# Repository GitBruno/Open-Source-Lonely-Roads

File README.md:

# Open Source Lonely Roads
An active linear power distribution board for Eurorack.

> __WARNING!__ ⚡️ Please be aware of the risks associated with electronics and take relevant precautions.

## Features
- High voltage distribution boards
- Dedicated linear regulators for each header
- Switchable status LEDs
- Star grounding on dedicated layer
- Wide traces
- Reverse voltage protection
- Bypass capacitors
- Ultra low noise
- Ultra low inter-module noise
- Protection + safety features
- 3u boat compatible
- Standard 84hp (19”) and 104hp compatible
- Wide range of voltage input options
- Multiple CV/Gate busses possible. (Have conflicting modules play nice together)
- Optional addons (Voltage converter/startup delay)

Please read the [Wiki](https://github.com/GitBruno/Open-Source-Lonely-Roads/wiki) to find out more about this project.

## Licence
Open Source Lonely Roads by [Robert D Jordan](http://www.catfullofghosts.com/) and [Bruno Herfst](http://brunoherfst.com/) is licensed under a [Creative Commons Attribution 4.0 International License](LICENCE.md).

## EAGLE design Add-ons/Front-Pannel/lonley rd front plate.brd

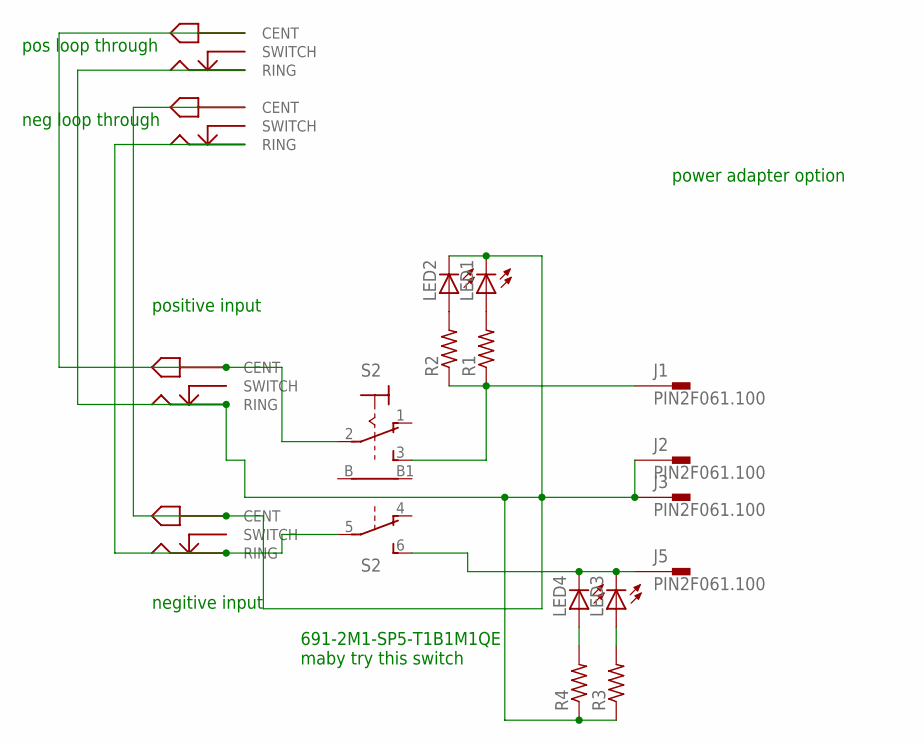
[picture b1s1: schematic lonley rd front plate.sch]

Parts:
J1, J2, J3, J5: PIN2F061.100; F061.100
LED1, LED2, LED3, LED4: LED3MM
R1, R2, R3, R4: R-US_0309/V; 0309V
S2: 9070-2W
U$1, U$2, U$3, U$4: PJ-066A_DC_JACK

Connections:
unnamed: LED2.A, R2.2
unnamed: J2.A1, J2.A2, J3.A1, J3.A2, LED1.K (C), LED2.K (C), R3.1, R4.1, U$1.RING, U$2.CENT, U$3.RING, U$4.CENT
unnamed: J1.A1, J1.A2, R1.1, R2.1, S2.3 (S)
unnamed: J5.A1, J5.A2, LED3.K (C), LED4.K (C)
unnamed: S2.2, U$1.CENT, U$3.CENT
unnamed: U$2.RING, U$4.RING
unnamed: LED1.A, R1.2
unnamed: LED3.A, R3.2
unnamed: LED4.A, R4.2

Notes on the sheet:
positive input
negitive input
pos loop through
neg loop through
691-2M1-SP5-T1B1M1QE maby try this switch
power adapter option

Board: 2 copper layers, 17 parts (0 on the bottom side), 9 nets, no tracks yet.

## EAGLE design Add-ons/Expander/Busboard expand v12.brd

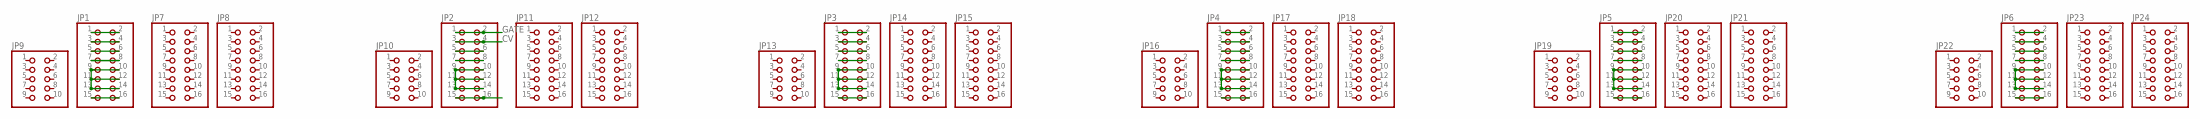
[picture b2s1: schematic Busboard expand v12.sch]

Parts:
JP1, JP2, JP3, JP4, JP5, JP6: PINHD-2X8; 2X08
JP7, JP8, JP11, JP12, JP14, JP15, JP17, JP18, JP20, JP21, JP23, JP24: PINHD-2X8/90; 2X08/90
JP9, JP10, JP13, JP16, JP19, JP22: PINHD-2X5; 2X05

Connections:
CV: JP1.3, JP1.4, JP2.3, JP2.4, JP3.3, JP3.4, JP4.3, JP4.4, JP5.3, JP5.4, JP6.3, JP6.4
GATE: JP1.1, JP1.2, JP2.1, JP2.2, JP3.1, JP3.2, JP4.1, JP4.2, JP5.1, JP5.2, JP6.1, JP6.2
unnamed: JP2.9, JP2.10, JP2.11, JP2.12, JP2.13, JP2.14
unnamed: JP3.9, JP3.10, JP3.11, JP3.12, JP3.13, JP3.14
unnamed: JP1.9, JP1.10, JP1.11, JP1.12, JP1.13, JP1.14
unnamed: JP3.15, JP3.16
unnamed: JP4.9, JP4.10, JP4.11, JP4.12, JP4.13, JP4.14
unnamed: JP1.15, JP1.16
unnamed: JP5.9, JP5.10, JP5.11, JP5.12, JP5.13, JP5.14
unnamed: JP1.7, JP1.8
unnamed: JP4.15, JP4.16
unnamed: JP6.9, JP6.10, JP6.11, JP6.12, JP6.13, JP6.14
unnamed: JP6.15, JP6.16
unnamed: JP6.7, JP6.8
unnamed: JP2.15, JP2.16
unnamed: JP2.5, JP2.6
unnamed: JP1.5, JP1.6
unnamed: JP2.7, JP2.8
unnamed: JP3.5, JP3.6
unnamed: JP5.15, JP5.16
unnamed: JP5.7, JP5.8
unnamed: JP3.7, JP3.8
unnamed: JP4.7, JP4.8
unnamed: JP4.5, JP4.6
unnamed: JP5.5, JP5.6
unnamed: JP6.5, JP6.6

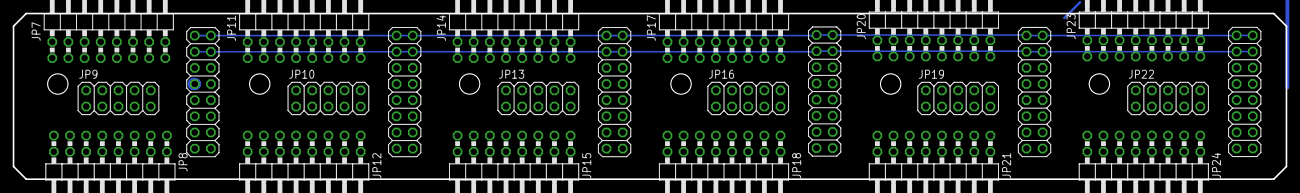
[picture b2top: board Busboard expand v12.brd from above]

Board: 2 copper layers, 200.2 x 26.1 mm, 24 parts (0 on the bottom side), 26 nets.

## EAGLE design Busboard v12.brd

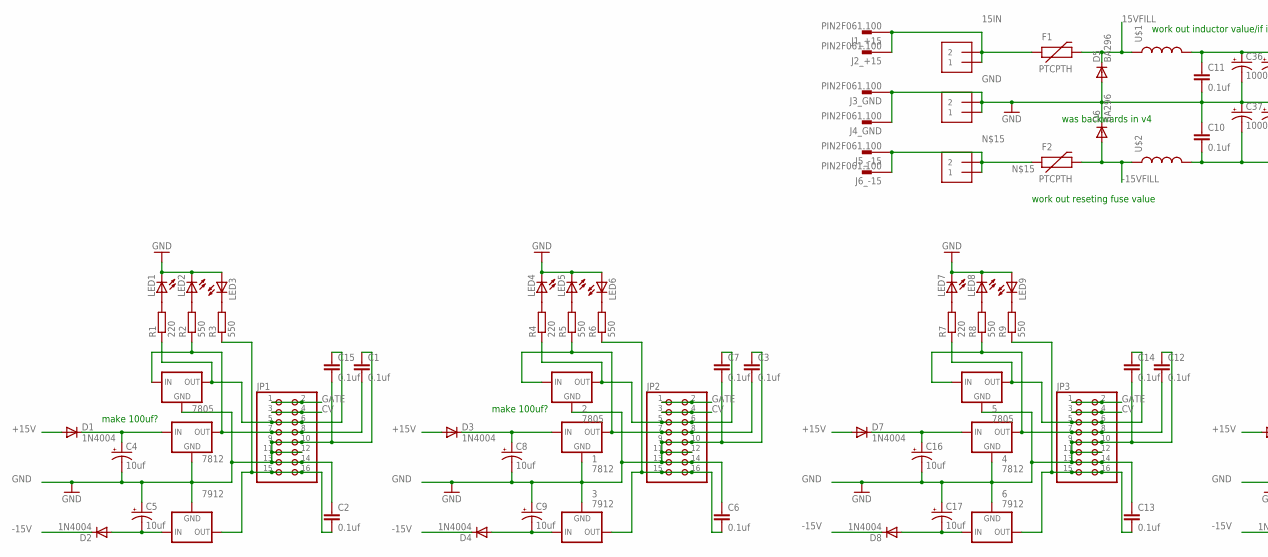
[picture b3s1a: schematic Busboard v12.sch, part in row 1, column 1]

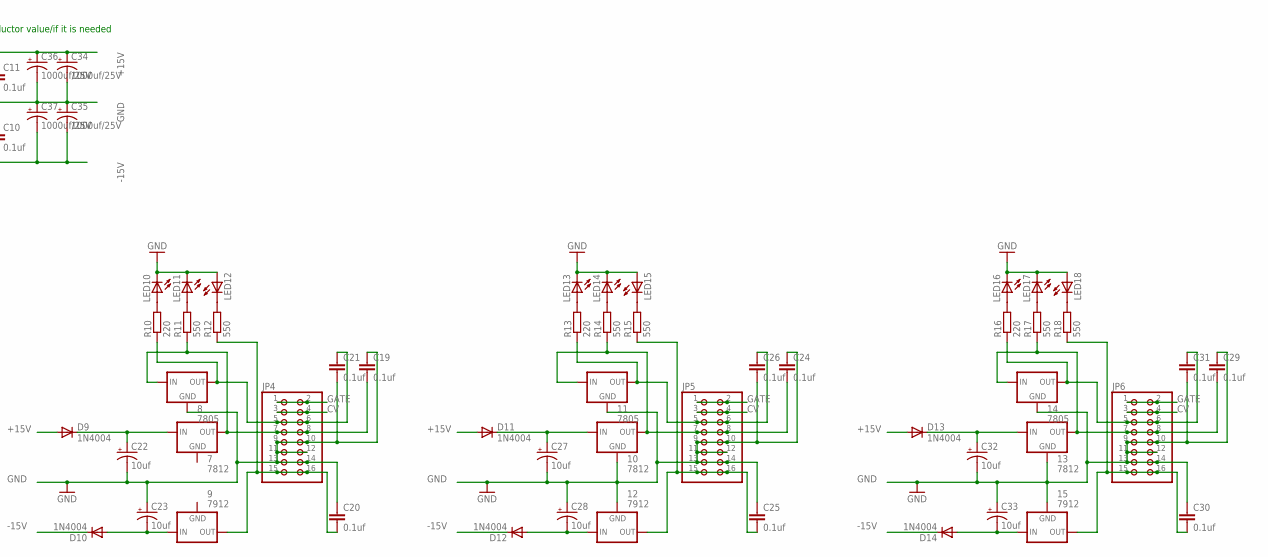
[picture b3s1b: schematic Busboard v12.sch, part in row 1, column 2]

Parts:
1, 4, 7, 10, 13: 7812; 78MXXS
2, 5, 8, 11, 14: 7805; 78MXXS
3, 6, 9, 12, 15: 7912; 79XXS
7805, 7812: 78MXXS
7912: 79XXS
+15V: 1X2-3.5MM
-15V: 1X2-3.5MM
C1, C2, C3, C6, C7, C10, C11, C12, C13, C14, C15, C19, C20, C21, C24, C25, C26, C29, C30, C31: 0.1uf; CAP-PTH-SMALL-KIT
C4, C5, C8, C9, C16, C17, C22, C23, C27, C28, C32, C33: 10uf; CPOL-RADIAL-10UF-25V
C34, C35, C36, C37: 1000uf/25V; CPOL-RADIAL-1000UF-25V-KIT
D1, D2, D3, D4, D7, D8, D9, D10, D11, D12, D13, D14: 1N4004; DO41-10
D5, D6: BA296; P2-15
F1, F2: PTCPTH; PTC
GND: 1X2-3.5MM
J1_+15, J2_+15, J3_GND, J4_GND, J5_-15, J6_-15: PIN2F061.100; F061.100
JP1, JP2, JP3, JP4, JP5, JP6: PINHD-2X8; 2X08
LED1, LED2, LED3, LED4, LED5, LED6, LED7, LED8, LED9, LED10, LED11, LED12, LED13, LED14, LED15, LED16, LED17, LED18: LED3MM
R1, R4, R7, R10, R13, R16: 220; 0207/5V
R2, R3, R5, R6, R8, R9, R11, R12, R14, R15, R17, R18: 550; 0207/5V
U$1, U$2: INDUCTORRLB0912; RLB0912

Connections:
15IN: +15V.1, +15V.2, F1.P$1 (1), J1_+15.A1, J1_+15.A2, J2_+15.A1, J2_+15.A2
15VFILL: D5.C, F1.P$2 (2), U$1.1
+15V: C11.1, C34.+, C36.+, D1.A, D3.A, D7.A, D9.A, D11.A, D13.A, U$1.2
-15V: C10.2, C35.-, C37.-, D2.C, D4.C, D8.C, D10.C, D12.C, D14.C, U$2.2
-15VFILL: D6.A, F2.P$2 (2), U$2.1
CV: JP1.3, JP1.4, JP2.3, JP2.4, JP3.3, JP3.4, JP4.3, JP4.4, JP5.3, JP5.4, JP6.3, JP6.4
GATE: JP1.1, JP1.2, JP2.1, JP2.2, JP3.1, JP3.2, JP4.1, JP4.2, JP5.1, JP5.2, JP6.1, JP6.2
GND: 1.GND, 2.GND, 3.GND, 4.GND, 5.GND, 6.GND, 8.GND, 10.GND, 11.GND, 12.GND, 13.GND, 14.GND, 15.GND, 7805.GND, 7812.GND, 7912.GND, C1.1, C2.1, C3.1, C4.2 (-), C5.1 (+), C6.1, C7.2, C8.2 (-), C9.1 (+), C10.1, C11.2, C12.1, C13.1, C14.2, C15.2, C16.2 (-), C17.1 (+), C19.1, C20.1, C21.2, C22.2 (-), C23.1 (+), C24.1, C25.1, C26.2, C27.2 (-), C28.1 (+), C29.1, C30.1, C31.2, C32.2 (-), C33.1 (+), C34.-, C35.+, C36.-, C37.+, D5.A, D6.C, GND.1, GND.2, J3_GND.A1, J3_GND.A2, J4_GND.A1, J4_GND.A2, JP1.9, JP1.10, JP1.11, JP1.12, JP1.13, JP1.14, JP2.9, JP2.10, JP2.11, JP2.12, JP2.13, JP2.14, JP3.9, JP3.10, JP3.11, JP3.12, JP3.13, JP3.14, JP4.9, JP4.10, JP4.11, JP4.12, JP4.13, JP4.14, JP5.9, JP5.10, JP5.11, JP5.12, JP5.13, JP5.14, JP6.9, JP6.10, JP6.11, JP6.12, JP6.13, JP6.14, LED1.K (C), LED2.K (C), LED3.A, LED4.K (C), LED5.K (C), LED6.A, LED7.K (C), LED8.K (C), LED9.A, LED10.K (C), LED11.K (C), LED12.A, LED13.K (C), LED14.K (C), LED15.A, LED16.K (C), LED17.K (C), LED18.A
unnamed: 7912.IN, C5.2 (-), D2.A
unnamed: 7912.OUT, C2.2, JP1.15, JP1.16, R3.1
unnamed: 6.OUT, C13.2, JP3.15, JP3.16, R9.1
unnamed: 7812.IN, C4.1 (+), D1.C
unnamed: 7805.IN, 7812.OUT, C1.2, JP1.7, JP1.8, R2.1
unnamed: 3.OUT, C6.2, JP2.15, JP2.16, R6.1
unnamed: 6.IN, C17.2 (-), D8.A
unnamed: 3.IN, C9.2 (-), D4.A
unnamed: 1.IN, C8.1 (+), D3.C
unnamed: LED1.A, R1.2
unnamed: LED2.A, R2.2
unnamed: -15V.1, -15V.2, F2.P$1 (1), J5_-15.A1, J5_-15.A2, J6_-15.A1, J6_-15.A2
unnamed: LED3.K (C), R3.2
unnamed: 1.OUT, 2.IN, C3.2, JP2.7, JP2.8, R5.1
unnamed: 4.IN, C16.1 (+), D7.C
unnamed: 2.OUT, C7.1, JP2.5, JP2.6, R4.1
unnamed: 7805.OUT, C15.1, JP1.5, JP1.6, R1.1
unnamed: LED4.A, R4.2
unnamed: LED5.A, R5.2
unnamed: LED6.K (C), R6.2
unnamed: 4.OUT, 5.IN, C12.2, JP3.7, JP3.8, R8.1
unnamed: 5.OUT, C14.1, JP3.5, JP3.6, R7.1
unnamed: LED7.A, R7.2
unnamed: LED8.A, R8.2
unnamed: LED9.K (C), R9.2
unnamed: 9.OUT, C20.2, JP4.15, JP4.16, R12.1
unnamed: 9.IN, C23.2 (-), D10.A
unnamed: 7.IN, C22.1 (+), D9.C
unnamed: 7.OUT, 8.IN, C19.2, JP4.7, JP4.8, R11.1
unnamed: 8.OUT, C21.1, JP4.5, JP4.6, R10.1
unnamed: LED10.A, R10.2
unnamed: LED11.A, R11.2
unnamed: LED12.K (C), R12.2
unnamed: 15.OUT, C30.2, JP6.15, JP6.16, R18.1
unnamed: 12.OUT, C25.2, JP5.15, JP5.16, R15.1
unnamed: 12.IN, C28.2 (-), D12.A
unnamed: 10.IN, C27.1 (+), D11.C
unnamed: 10.OUT, 11.IN, C24.2, JP5.7, JP5.8, R14.1
unnamed: 11.OUT, C26.1, JP5.5, JP5.6, R13.1
unnamed: LED13.A, R13.2
unnamed: LED14.A, R14.2
unnamed: LED15.K (C), R15.2
unnamed: 15.IN, C33.2 (-), D14.A
unnamed: 13.IN, C32.1 (+), D13.C
unnamed: 13.OUT, 14.IN, C29.2, JP6.7, JP6.8, R17.1
unnamed: 14.OUT, C31.1, JP6.5, JP6.6, R16.1
unnamed: LED16.A, R16.2
unnamed: LED17.A, R17.2
unnamed: LED18.K (C), R18.2

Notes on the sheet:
work out reseting fuse value
work out inductor value/if it is needed
was backwards in v4
make 100uf?

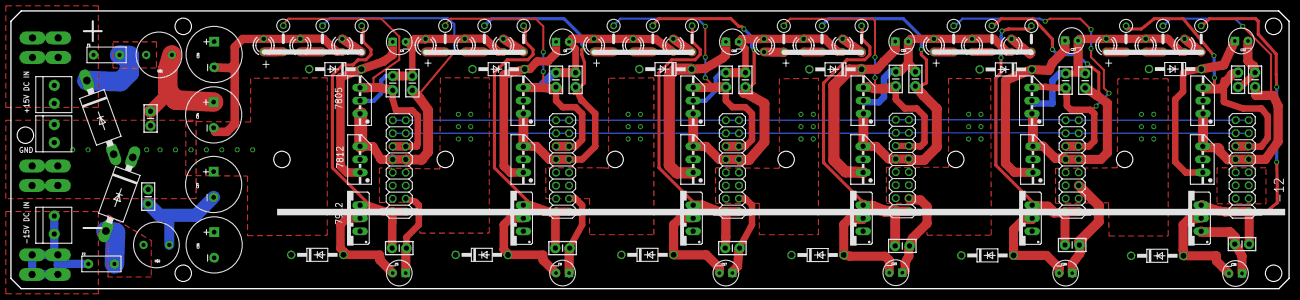
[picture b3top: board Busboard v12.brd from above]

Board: 2 copper layers, 248.5 x 54.0 mm, 123 parts (0 on the bottom side), 57 nets.

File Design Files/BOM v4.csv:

"Qty","Part Number","Description","Package","Manufacturer","Suggested Suppliers","Mouser Part No","Sub/Comments","Part ID."
"6","","Headers","2X08"," "," ","-"," ","JP1,JP2,JP3,JP4,JP5,JP6"
"6","7805","Voltage Regulator","78MXXS"," "," ","511-L7805CV"," ","7805,2,5,8,11,14"
"6","7812","Voltage Regulator","78MXXS"," "," ","511-L7812CV"," ","7812,1,4,7,10,13"
"6","7912","Voltage Regulator","79XXS"," "," ","926-LM7912CT/NOPB"," ","3,6,9,12,15,7912"
"6","220","Resistor","0207/5V"," "," ","594-5073NW220R0J"," ","R1,R4,R7,R10,R13,R16"
"12","550","Resistor","0207/5V"," "," ","71-CPF1500R00FKE14","Arround 500/510 is fine too","R2,R3,R5,R6,R8,R9,R11,R12,R14,R15,R17,R18"
"3","","Terminal","BANANA_CONN"," "," ","651-1985865"," ","SCREW_+15,SCREW_-15,SCREW_GND"
"18","0.1uf","Capacitor","CAP-PTH-SMALL-KIT"," "," ","810-FG26C0G2A104JRT6"," ","C1,C2,C3,C6,C7,C12,C13,C14,C15,C19,C20,C21,C24,C25,C26,C29,C30,C31"
"12","10uf","Capacitor","CPOL-RADIAL-10UF-25V"," "," ","647-UPW1E100MDD6"," ","C4,C5,C8,C9,C16,C17,C22,C23,C27,C28,C32,C33"
"3","100uf","Capacitor","CPOL-RADIAL-100UF-25V"," "," ","647-UVY1E101MDD"," ","C10,C11,C18"
"12","1N4004","Diode","DO41-10"," "," ","621-1N4004"," ","D1,D2,D3,D4,D7,D8,D9,D10,D11,D12,D13,D14"
"1","","Switch","EG1218"," "," ","612-EG1218"," ","S1"
"6","PIN2F061.200","Terminal","F061.200"," "," ","571-624091"," ","J1_+15,J2_+15,J3_GND,J4_GND,J5_-15,J6_-15"
"18","","LED","LED3MM"," "," ","696-SSF-LX3P74GD"," ","LED1,LED2,LED3,LED4,LED5,LED6,LED7,LED8,LED9,LED10,LED11,LED12,LED13,LED14,LED15,LED16,LED17,LED18"
"2","BA296","Rectifier","P2-15"," "," ","833-1N5400-TP"," ","D5,D6"
"2","PTCPTH","Reseting Fuse","PTC"," "," ","-","work out fuse value","F1,F2"
"2","","Inductor","RLB0912"," "," ","-","work out value/if needed","U$1,U$2"

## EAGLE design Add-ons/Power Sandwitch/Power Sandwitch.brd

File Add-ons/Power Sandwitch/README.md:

# Power Sandwitch
An add-on for the Open Source Lonely Roads power distribution boards. This add-on makes the OSLR boards eat a wide variety of power supplies. 

So besides any +- 15v cage power supply the OSLR can be powered off:

- Single 9-18v DC supply
- Dual 15+v DC supplies (E.g. 2 laptop chargers)
- Single 14-36v supply (Cheap!)

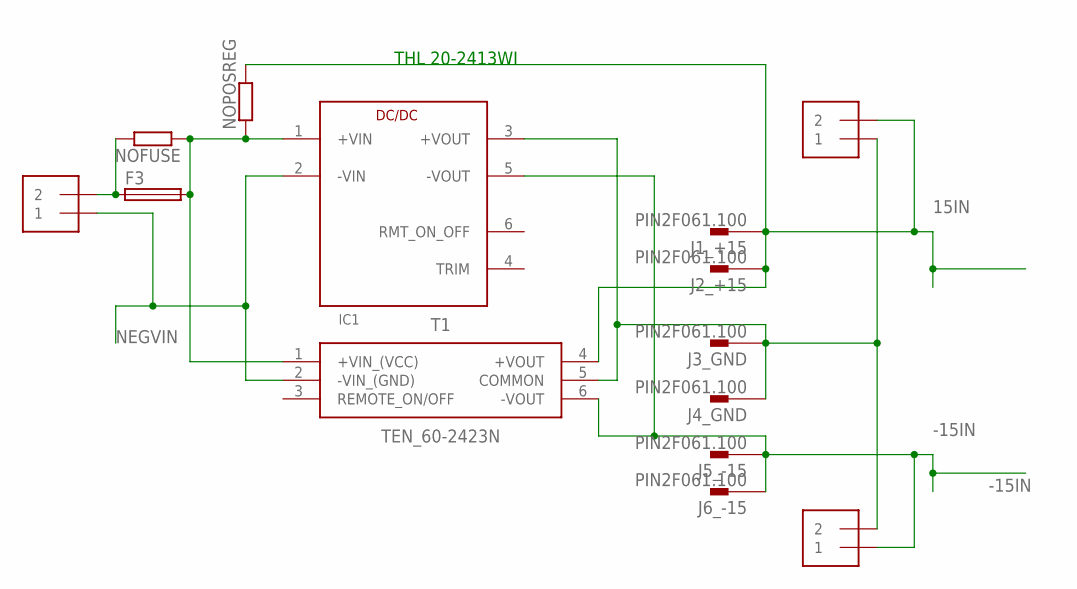
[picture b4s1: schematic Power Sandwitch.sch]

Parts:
DC_IN, DC_IN1, DC_IN2: 1X2-3.5MM
F3: GSH15
IC1: THL_20WI_SERIES
J1_+15, J2_+15, J3_GND, J4_GND, J5_-15, J6_-15: PIN2F061.100; F061.100
NOFUSE: SMT-REF
NOPOSREG: SMT-REF
T1: TEN_60-2423N; TEN60-2423N

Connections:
15IN: DC_IN1.2, J1_+15.A1, J1_+15.A2, J2_+15.A1, J2_+15.A2, NOPOSREG.1, T1.4 (+VOUT)
-15IN: DC_IN2.1, IC1.5 (-VOUT), J5_-15.A1, J5_-15.A2, J6_-15.A1, J6_-15.A2, T1.6 (-VOUT)
unnamed: DC_IN1.1, DC_IN2.2, IC1.3 (+VOUT), J3_GND.A1, J3_GND.A2, J4_GND.A1, J4_GND.A2, T1.5 (COMMON)
unnamed: F3.2, IC1.1 (+VIN), NOFUSE.2, NOPOSREG.2, T1.1 (+VIN_(VCC))
unnamed: DC_IN.2, F3.1, NOFUSE.1
NEGVIN: DC_IN.1, IC1.2 (-VIN), T1.2 (-VIN_(GND))

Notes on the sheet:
THL 20‑2413WI

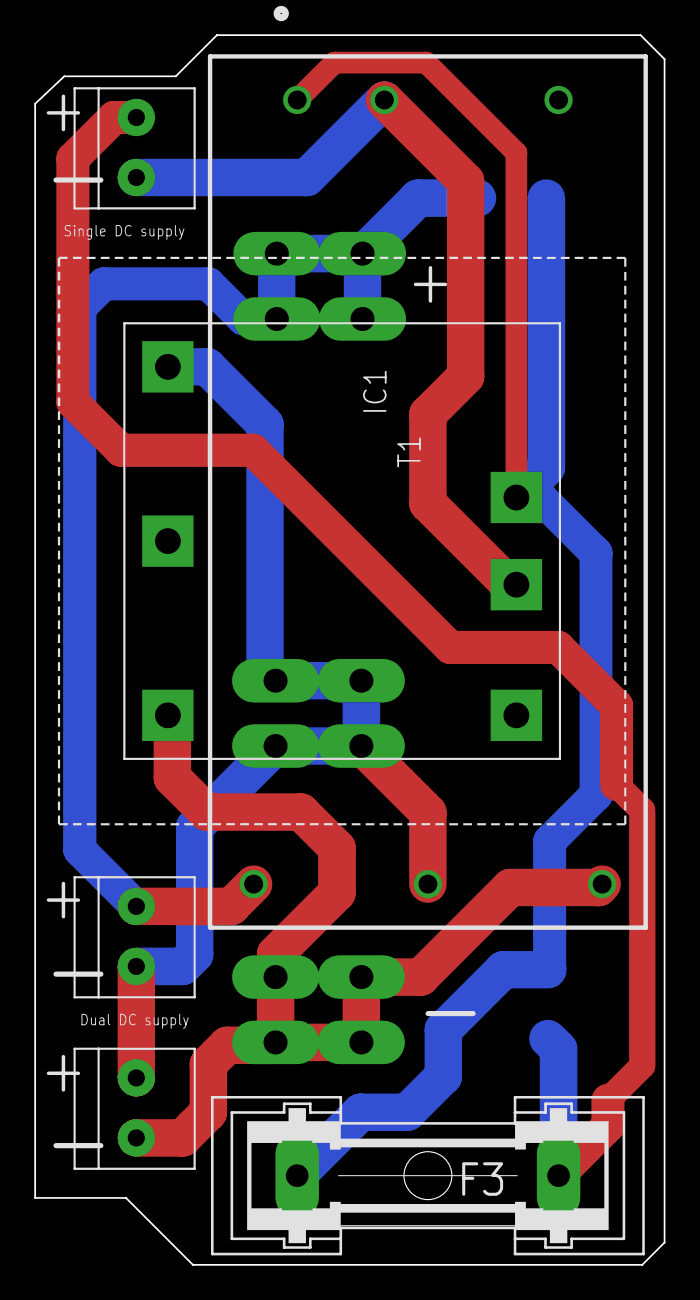
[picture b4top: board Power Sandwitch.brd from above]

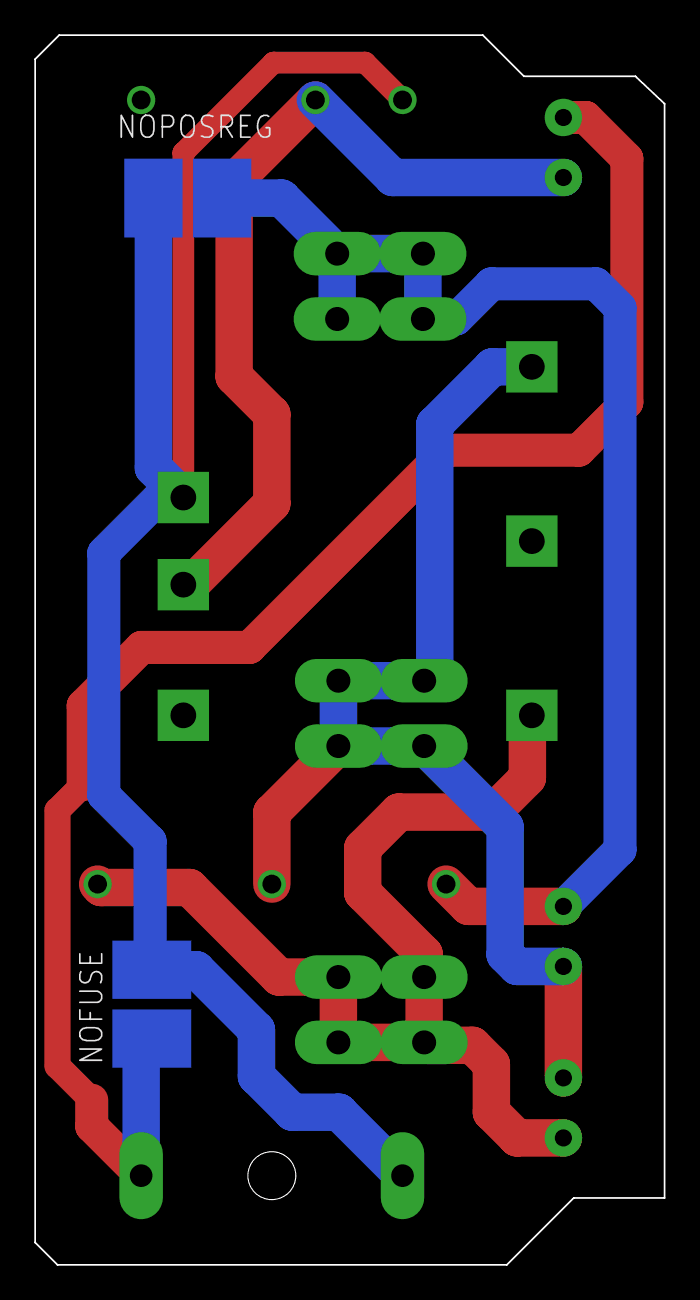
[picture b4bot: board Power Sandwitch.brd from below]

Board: 2 copper layers, 36.7 x 71.7 mm, 14 parts (2 on the bottom side), 6 nets.

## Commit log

2017-07-17 Added licence
2017-07-20 Update and rename Goals & todo.txt to Goals & Todo.md
    Formatted to md so it looks good. We will still need to define the goals further.
2017-07-21 Added price + formatting
2017-08-13 Add files via upload
    Here are the eagle files for the prototype busboard.
2017-08-13 Create gerb
2017-08-13 Create empty
2017-08-17 Update Schematic PDF to fit on page
2017-09-03 Start BOM
2017-09-05 Update BOM with mouser parts
2017-09-23 Create info
2017-09-23 Rename Design Files/Busboard v4.sch to Design Files/V4 files/Busboard v4.sch
2017-09-23 Rename Design Files/Busboard v4.brd to Design Files/V4 files/Busboard v4.brd
2017-09-23 Rename Design Files/BOM v4.csv to Design Files/V4 files/BOM v4.csv
2017-09-23 Delete Busboard v4 Board.pdf
    moved to sub directory
2017-09-23 Add files via upload
    pdf for board design v4
2017-09-23 Delete Busboard v4 Schematic.pdf
    moving to sub folder to make way for v5
2017-09-23 Rename Design Files/gerb v4/Busboard v4.GBL to Design Files/gerb v4/V4 files/gerb v4/Busboard v4.GBL
2017-09-23 Delete Busboard v4.GBO
    has error, dont want people using it
2017-09-23 Delete Busboard v4.GML
    has error, don't want people using it
2017-09-23 Delete Busboard v4.GBL
    has error, don't want people using it
2017-09-23 Delete Busboard v4.GTL
    has error, don't want people using it
2017-09-23 Delete Busboard v4.GTO
    has error, don't want people using it
2017-09-23 Delete Busboard v4.GTP
    has error, don't want people using it
2017-09-23 Delete Busboard v4.GTS
    has error, don't want people using it
2017-09-23 Delete Busboard v4.TXT
    has error, don't want people using it
2017-09-23 Delete Busboard v4.dri
    has error, don't want people using it
2017-09-23 Delete Busboard v4.gpi
    has error, don't want people using it
2017-09-23 Add files via upload
    V5 files with the last port wiring fixed
2017-09-26 Update Goals & Todo.md
    2xpcb errors fixed
2017-09-26 Update Goals & Todo.md
    magic smoke from an input cap
2017-10-04 updated Bom
2017-10-15 Set theme jekyll-theme-hacker
2017-10-15 Set theme jekyll-theme-tactile
2017-11-14 the finished files for v10
    i couldn't seem to open any of the graphics files to add them, but found a good tourotrial for adding graphics as svg's which look stones easyer, Open source logo is on there tho
    https://learn.sparkfun.com/tutorials/importing-custom-images-into-eagle/all
2017-11-17 Cleaning
2017-12-03 v12
    - Aligned mounting holes
    - All LEDS same orientation
2017-12-10 Added OSLR + OSHWA marks
2017-12-10 Add mounting template
2017-12-14 updated .sch and .brd
    i did another check over everything to make sure it lined up with the power sandwich, and added a 0.1uf 50v cap just after the inductor/ferrite bead to hopefully reduce ripple at the input.
2017-12-14 Update README.md
    got to check the reg inputs but i think this is the specs for the single negative rail regulator.
2017-12-14 Add files via upload
    latest power sandwitch files updated
2018-01-05 updated with latest parts
2018-01-19 Add files via upload
    Fixing some dumb mistakes based on building the v12 prototype. had some backward caps and should have picked a lower trip thresh for the polyfuse.
2018-01-19 Create info.txt
    new product expantion
2018-01-19 Add files via upload
    need to check there is no collision with the 1000uf caps on the .brd file
2019-04-15 Add AWG logo

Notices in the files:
parts and their libraries:
SparkFun-Capacitors: Licensing: Creative Commons ShareAlike 4.0 International - https://creativecommons.org/licenses/by-sa/4.0
